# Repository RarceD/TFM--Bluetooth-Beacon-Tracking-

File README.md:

# Introduction #
BLE tracking system based on ESP32 uC and nrf52832 iBeacon. The main idea is to stablish a net of beacons which
comunicate with the ESP32 masters via Bluetooth Low Energy on Beacon Mode.

Every beacon wake up every 1200ms and send their uuid, mayor, minor, battery and rssi. The most important parameter is the rssi because with that we can calculate the distance between masters and I can positionate them on a map.

The visualize tool is made with Python and Pygame, all the masters send data to a free to use broker and the console is listenning incoming messages in order to calculate the distance and situate them on the static map.
## Hardware ##
### ESP32 master and  nrf52832 ###
I have develop a simple esp32 board that can be powered via 220@VAC and every minute it listen to the slaves and calculate the distance between beacons.
| Board Specifications  |  ESP32 WROVER       |  nrf52832          |
| :--------------------:|:-------------------:| :----------------: | 
| Flash                 |         448kB       |      256 kB        | 
| RAM                   |        520kB        |       32 kB        | 
| Consumption on sleep  |         10uA        |    1.9 μA at 3 V   | 

### Images beacon ###
In the following image we can see the pcb of the esp32 beacon device and the master esp32 pcb:

The real boards:

### Images master listener ###
Kicad files also included:

The real boards:

## Software ##
### Trilateration ###
If two elements on a net are listened by two masters the algorithm will calculate the middle distance of both of them acording to the strengh of the signal received. Appling trilateration we can obtein the position between three masters and only one beacon sending data. I don't cosider more than 3 masters detected the same beacon.

## 3D Printing ##
The electronics need a case in order not to be touch by no people, thats why I have design a simple model in Freecad:

## Visualizer ##
For making the fastest prototype of the visualization tool I have program a pygame console that is connected to mqtt and always listening to the master messages.
I'm using free mqtt broker: 
```python 
 broker_address = "broker.mqttdashboard.com"
```
It has fall out just one time in more than 3 months, it seems right.

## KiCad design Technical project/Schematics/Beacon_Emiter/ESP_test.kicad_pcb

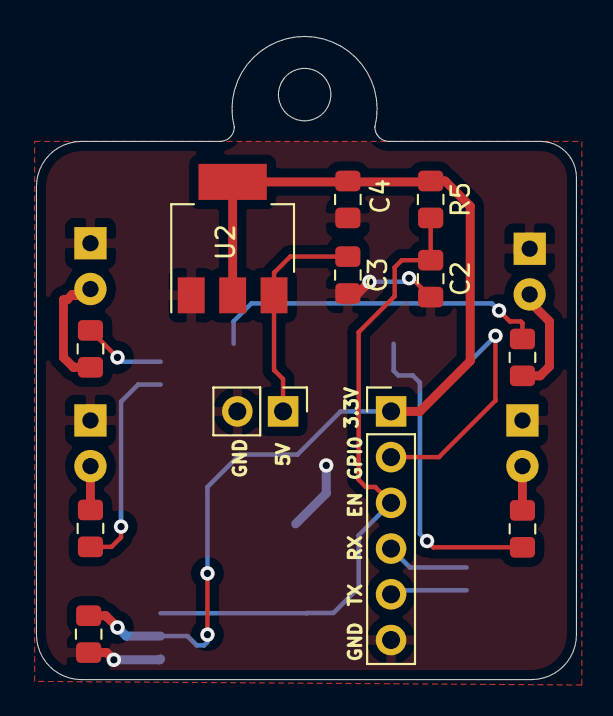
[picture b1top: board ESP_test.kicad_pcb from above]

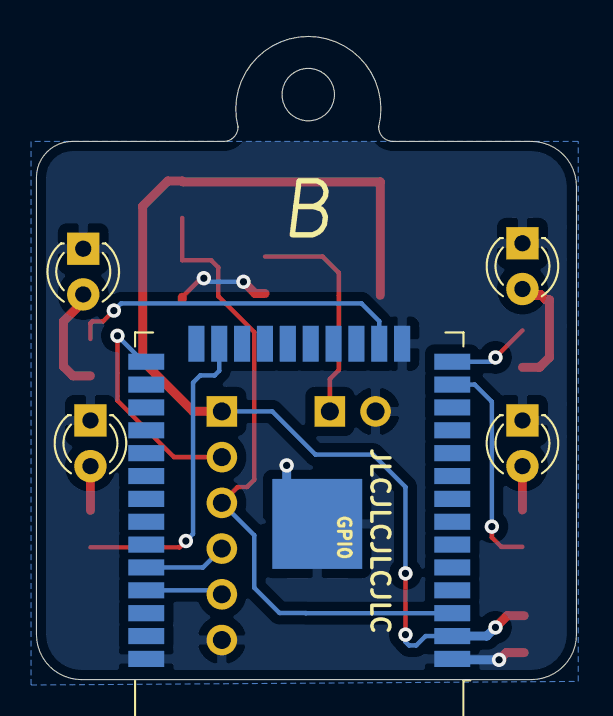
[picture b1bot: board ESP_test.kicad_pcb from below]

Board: 2 copper layers, 30.0 x 35.7 mm, 17 parts (5 on the bottom side), 15 nets.

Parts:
C1: C; C_0805_2012Metric_Pad1.15x1.40mm_HandSolder
C2: 0.1u; C_0805_2012Metric_Pad1.15x1.40mm_HandSolder
C3, C4: 10u; C_0805_2012Metric_Pad1.15x1.40mm_HandSolder
D1, D2, D3, D4: LED; LED_D3.0mm_Clear
J1: Conn_01x06_Female; PinHeader_1x06_P2.54mm_Vertical
J2: Conn_01x02_Female; PinHeader_1x02_P2.54mm_Vertical
R1, R2, R3, R4: R; R_0805_2012Metric_Pad1.15x1.40mm_HandSolder
R5: 10k; R_0805_2012Metric_Pad1.15x1.40mm_HandSolder
U1: ESP32-WROOM-32
U2: AMS1117-3.3; SOT-223-3_TabPin2

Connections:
EN: C2.1, J1.3, R5.2, U1.3
GND: C1.2, C2.2, C3.2, C4.2, D1.1, D2.1, D3.1, D4.1, J1.6, J2.2, U1.1, U1.15, U1.38, U1.39, U2.1
GPIO0: J1.2, U1.25
LED: R1.1, U1.14
LED2: R2.1, U1.16
LED3: R3.1, U1.13
LED4: R4.1, U1.23
unnamed: C3.1, J2.1, U2.3
unnamed: D1.2, R1.2
unnamed: D2.2, R2.2
unnamed: D3.2, R3.2
unnamed: D4.2, R4.2
RX: J1.4, U1.34
TX: J1.5, U1.35
VCC: C1.1, C4.1, J1.1, R5.1, U1.2, U2.2

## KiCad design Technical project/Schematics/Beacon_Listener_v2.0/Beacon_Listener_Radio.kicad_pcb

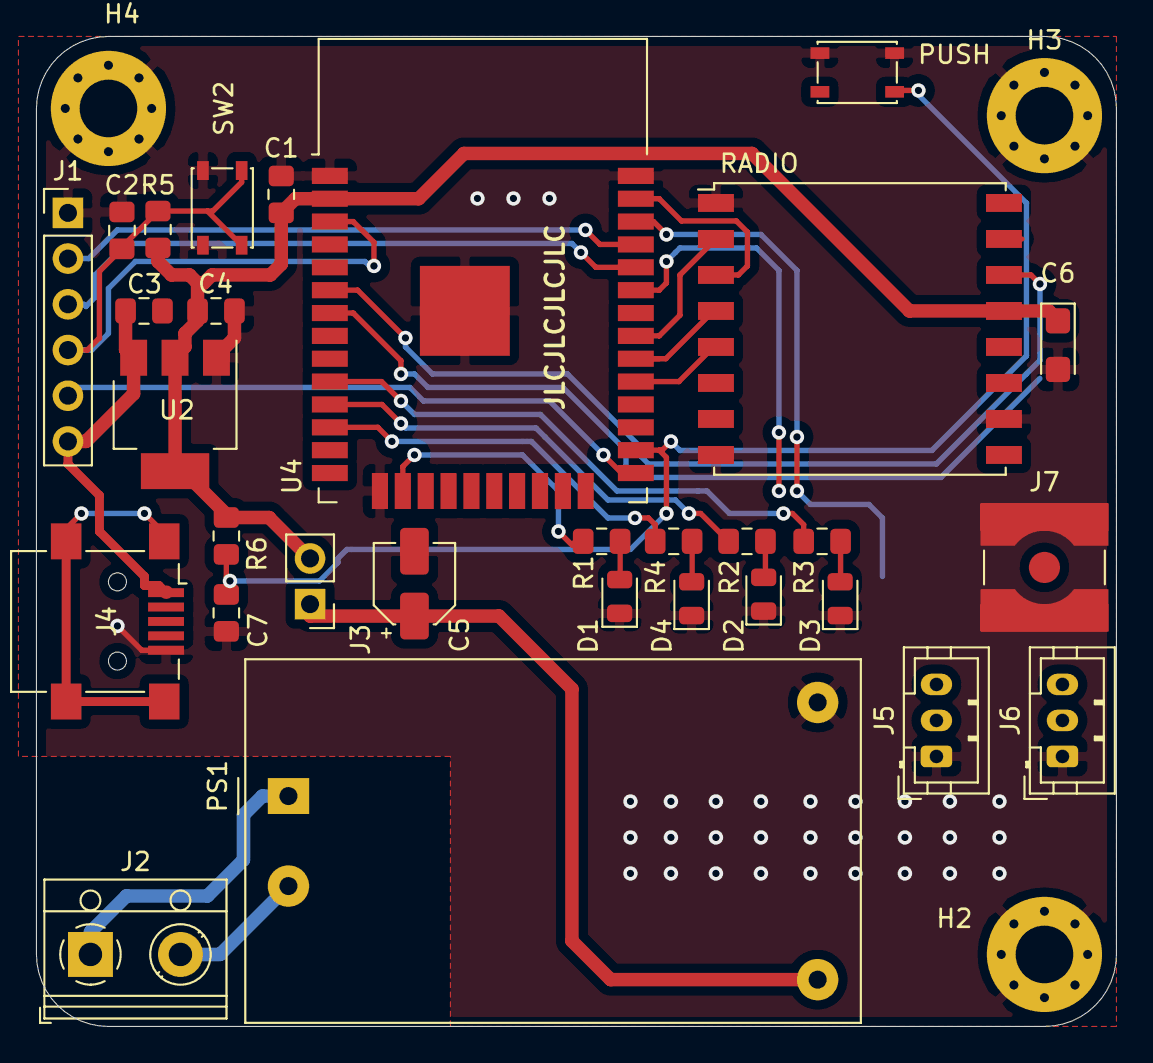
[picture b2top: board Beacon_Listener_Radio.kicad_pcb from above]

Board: 2 copper layers, 60.0 x 55.0 mm, 33 parts (0 on the bottom side), 30 nets.

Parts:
C1, C3, C4: 10u; C_0805_2012Metric_Pad1.15x1.40mm_HandSolder
C2, C7: 0.1u; C_0805_2012Metric_Pad1.15x1.40mm_HandSolder
C5: 10u; CP_Elec_4x5.3
C6: CP; CP_EIA-3216-10_Kemet-I
D1, D2, D3, D4: LED; LED_0805_2012Metric
H2, H3, H4: MountingHole_Pad; MountingHole_3.2mm_M3_Pad_Via
J1: Conn_01x06_Female; PinHeader_1x06_P2.54mm_Vertical
J2: input AC; TerminalBlock_RND_205-00012_1x02_P5.00mm_Horizontal
J3: select if usb or AC power; PinHeader_1x02_P2.54mm_Vertical
J4: USB_B_Micro; USB_Mini-B_Lumberg_2486_01_Horizontal
J5, J6: Conn_01x03_Male; JST_PH_B3B-PH-K_1x03_P2.00mm_Vertical
J7: Conn_Coaxial; SMA_Amphenol_132134-10_Vertical
PS1: HLK-PM03; Converter_ACDC_HiLink_HLK-PMxx
PUSH: SW_Push; SW_SPST_PTS810
R1, R2, R3, R4: 1k; R_0805_2012Metric_Pad1.15x1.40mm_HandSolder
R5, R6: 10k; R_0805_2012Metric_Pad1.15x1.40mm_HandSolder
RADIO: RFM95W-868S2; HOPERF_RFM9XW_SMD
SW2: SW_Push; SW_SPST_PTS810
U2: AMS1117-3.3; SOT-223-3_TabPin2
U4: ESP32-WROOM-32

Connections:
+3V3: C1.1, C4.1, C6.1, J3.2, R5.1, R6.1, RADIO.13, U2.2, U4.2
+5V: C3.1, J1.6, J4.1, U2.3
AC: J2.1, PS1.1
CS_RF: RADIO.5, U4.29
ConfigButton: C7.1, PUSH.1, R6.2, U4.26
EN: C2.1, J1.4, R5.2, SW2.1, U4.3
GND: C1.2, C2.2, C3.2, C4.2, C5.2, C6.2, C7.2, D1.1, D2.1, D3.1, D4.1, H2.1, H3.1, H4.1, J1.1, J4.5, J5.1, J6.1, J7.2, PS1.3, PUSH.2, RADIO.1, RADIO.8, RADIO.10, SW2.2, U2.1, U4.1, U4.15, U4.38, U4.39
GNDPWR: J2.2, PS1.2
GPIO0: J1.5, U4.25
INT_CAD: RADIO.15, U4.7
LED: R1.1, U4.16
LED2: R2.1, U4.11
LED3: R3.1, U4.10
LED4: R4.1, U4.12
MISO: RADIO.2, U4.31
MOSI: RADIO.3, U4.37
MainInput: C5.1, J3.1, PS1.4
unnamed: D1.2, R1.2
unnamed: D2.2, R2.2
unnamed: D3.2, R3.2
unnamed: D4.2, R4.2
unnamed: J7.1, RADIO.9
RF_INT: RADIO.14, U4.6
RX: J1.3, U4.34
RX_UART2: J5.3, U4.27
SCK: RADIO.4, U4.30
SCL: J6.3, U4.36
SDA: J6.2, U4.33
TX: J1.2, U4.35
TX_UART2: J5.2, U4.28

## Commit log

2020-09-13 conforming the idea
2020-09-25 search for specific device and led on
2020-09-25 send rssi via mqtt
2020-09-26 calculate the distance to the node and obtein the formula rssi-distance
2020-09-26 visualize tool for all the beacons
2020-09-27 create beacons received from mqtt
2020-09-27 beacon simulation done, TODO: correct saving process
2020-09-28 clear the code and performance
2020-10-03 simple but listen to mqtt and works
2020-10-03 fix do not save repeted mqtt msg on screen
2020-10-03 clearing and removing lagging code
2020-10-03 send the correct data to the backend, rssi and uuid
2020-10-04 checkBeacons function in progrees
2020-10-07 rssi calculator
2020-10-08 plot with matplotlib
2020-10-10 plot rssi in a table in order to filter
2020-10-10 plot 2 beacons better formatting
2020-10-10 technical memmory of the project
2020-10-11 deep sleep and then publish
2020-10-11 remove debug prints
2020-10-11 manualy stop the data adquisition
2020-10-11 beacon is not nrf, is also the esp32
2020-10-12 almost 100mA and 650ms on sending a beacon msg
2020-10-15 esp listen, publish and then sleep
2020-10-16 set the technical memmory layout to star the game
2020-10-17 apply a no uuid filter
2020-10-17 add rssi calculation formulas
2020-10-18 application layer and comparison
2020-10-18 beacon modes
2020-10-19 house map calculations
2020-10-21 frecuency study
2020-10-21 esp now reconsidering
2020-10-22 add esp now example and espnow
2020-10-22 trilateration
2020-10-24 invoice and ble characteristics
2020-10-24 antenna and better structured
2020-10-27 add schematics and gerbers
2020-10-27 create the pdf to show of
2020-10-28 create 2 more anexos about hardware and mechanics
2020-10-29 more pictures of the pcb and better mechanical anexo explained
2020-10-30 explaned all the justification memmory
2020-10-31 3/5 of the memmory
2020-10-31 invoices and finish the designs
2020-11-02 add graph index, pictures, and requirements
2020-11-02 plotting my house to test the tecnology
2020-11-02 can change the colors externally
2020-11-02 main listener code
2020-11-04 integration on the new board
2020-11-07 room and beacon configuration
2020-11-07 create a auto file room generator
2020-11-07 starting global calculations
2020-11-07 it doesn't recognise callback
2020-11-15 readme not ignored
2020-11-25 add all beacons just for receiving data
2020-11-27 add images and mechanical part memmory
2020-11-27 image table ok
2020-11-28 finish mechanical anexo
2020-11-28 hardware anexo finish
2020-11-28 hardware anexo mesh3 problem fix
2020-11-28 gantt van and tir
2020-11-29 memoria justificativa retoques antenas
2020-11-29 remove bugs on text and better formatting
2020-12-02 esp now send beacons data and sleep
2020-12-05 espnow not in setup
2020-12-05 BLE scanners and senders via ESPnow
2020-12-05 new pcb and this time with radio lora inside
2020-12-06 rf95 module
2020-12-07 visualize tool for my house
2020-12-07 supermarket rssi calculations with 2 esps
2020-12-07 calculate the intersection 2 circuferences
2020-12-08 locate 1 alone beacon and 2 trilateration
2020-12-08 trilateration 3 devices
2020-12-08 radio module include on the 2 version of pcb
2020-12-12 software anexo
2020-12-12 finish software anexo
2020-12-16 almost finish memmory
2020-12-16 fix readme
2020-12-16 readme image fix
2020-12-16 images
2020-12-19 front page for all the letters
2020-12-19 anexo de diseño de hardware - portada y revisado
2020-12-19 anexo mecánico formato y revisión
2020-12-19 formato de documentos y portadas
2020-12-19 finish formatting all elements
2020-12-19 fallo con archivos
2021-01-04 spelling mistakes of the 20 first pages
2021-01-06 more spelling mistakes
2021-01-16 bibliografía
2021-01-20 power point add especifications
2021-01-21 B revision
2021-01-23 more details on the memmory and power point
2021-01-24 ending and just one more week
2021-01-26 end memmory, waiting to the powerpoint
2021-01-27 send TFM
2021-02-08 end the power point, show on monday
